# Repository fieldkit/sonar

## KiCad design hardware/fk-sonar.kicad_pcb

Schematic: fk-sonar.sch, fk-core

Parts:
C1, C12: 4.7uF; CAP-0603
C2, C5, C7, C8, C9, C15, C16, C17, C19, C20: 100nF; CAP-0603
C3, C4: 18pF; CAP-0603
C6, C10, C11: 1uF; CAP-0603
C13: 4.7nF; CAP-0603
C14, C18: 10uF; CAP-0603
D1: Orange; LED-0603
D2: PRTR5V0U2X; SOT-143B
D3: Green; LED-0603
F1: MF-PSMF050X-2; MF-PSMF020X
J1: CONN_01x03; Molex_CLIK-Mate_502382-0370_1x03_P1.25mm_Vertical
J2: CONN_02x05_SWD; HDR_02x05_Pitch1.27mm_SMD_SWD
J3: MICRO-USB; USB_10118193-0001LF-core-mod
J4: MICRO-USB; USB_1051330011
J5, J7: CONN_01x02; SJ_OPEN
J6, J12, J13: CONN_01x04; Molex_CLIK-Mate_502382-0470_1x04_P1.25mm_Vertical
J8: CONN_01x03_SERIAL; Molex_CLIK-Mate_502382-0370_1x03_P1.25mm_Vertical
J9, J10: CONN_01x05; Molex_CLIK-Mate_502382-0570_1x05_P1.25mm_Vertical
J11: CONN_01x04; BM04B-SRSS-TB
L1, L2: BLM18KG221SN1D; IND-0603
M1, M3, M4, M6: MOUNT_HOLE; HOLE_NPTH_2.7MM
M2, M5: FIDUCIAL; FIDUCIAL-1MM
Q1: 2N7002LT1G; SOT-23
R1: 2K2; RES-0603
R2, R7, R9: 10K; RES-0603
R3, R5: 330R; RES-0603
R4: 1M; RES-0603
R6, R11, R12: 100K; RES-0603
R8, R10: ?; RES-0603
R13, R14, R15, R16: 4.7K; RES-0603
R17: 2k2; RES-0603
SW1: SPNO; SW_SPST_WURTH_1
U1: ATSAMD21G18A-AU; TQFP-48_7x7mm_Pitch0.5mm
U2: MCP1700T-3302E/MB; SOT-89
U3: TPS2052B; SOIC-8-N
U4: S25FL116K0XMFI041; SOIC-8-N-WIDE
U7: SK6812
Y1: FC-135; ABS07

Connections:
3V3: C5.1, C8.1, C9.1, C11.1, C15.1, D1.2, D3.2, J1.3, J2.1, J5.1, J7.1, J9.1, J10.1, L1.2, R2.1, R6.1, R7.2, R9.2, R13.2, R14.2, U1.17 (VDDIO), U1.36 (VDDIO), U1.44 (VDDIN), U2.3, U3.2, U7.3
5V0: C10.1, C12.1, L2.1, U2.2
/A0: U1.3 (PA02)
/A1: J1.2, U1.7 (PB08)
/A2: U1.8 (PB09)
/A3: U1.9 (PA04), U7.2
/A4: U1.10 (PA05)
/A5: U1.47 (PB02)
/D0: U1.16 (PA11)
/D1: U1.15 (PA10)
/D2_RADIO_CS: U1.23 (PA14)
/D5: U1.24 (PA15)
/D6_FLASH_CS: U1.29 (PA20), U4.1 (~CS~)
/D7_SENSOR_EN: R10.1, U1.30 (PA21), U3.4
/D8_PERIPH_EN: R8.1, U1.11 (PA06), U3.3
/D9: U1.12 (PA07)
/D10: U1.27 (PA18)
/D11: U1.25 (PA16)
/D12: U1.28 (PA19)
/D13: Q1.1, U1.26 (PA17)
/D30: J8.3 (D30), U1.37 (PB22)
/D31: J8.2 (D31), U1.38 (PB23)
/D38_RADIO_D0: U1.22 (PA13)
/MISO: U1.21 (PA12), U4.2 (SO/IO1)
/MOSI: U1.19 (PB10), U4.5 (SI/IO0)
/PERIPH_3V3: C14.1, C16.1, C20.1, J5.2, R11.1, U3.7, U4.3 (~WP~/IO2), U4.7 (~HOLD~/IO3), U4.8 (VCC)
/RESET: R3.1, U1.40 (RESETN)
/RST: C19.1, J2.10, R2.2, R3.2, SW1.2
/RX_LED: U1.48 (PB03)
/SCK: U1.20 (PB11), U4.6 (SCLK)
/SCL1: J6.3, J11.4, J12.3, J13.3, R16.1, U1.32 (PA23)
/SCL3: J9.4, J10.4, R14.1, U1.14 (PA09)
/SDA1: J6.4, J11.3, J12.4, J13.4, R15.1, U1.31 (PA22)
/SDA3: J9.5, J10.5, R13.1, U1.13 (PA08)
/SENSOR_3V3: C17.1, C18.1, J6.1, J7.2, J11.2, J12.1, J13.1, R12.1, R15.2, R16.2, U3.6
/SWCLK: J2.4, U1.45 (PA30)
/SWDIO: J2.2, U1.46 (PA31)
/TX_LED: U1.39 (PA27)
/USB+: D2.2, J3.3, J4.3, U1.34 (PA25)
/USB-: D2.3, J3.2, J4.2, U1.33 (PA24)
/USB_ID: R5.2, U1.41 (PA28)
GND: C1.2, C2.2, C3.1, C4.1, C5.2, C6.2, C7.2, C8.2, C9.2, C10.2, C11.2, C12.2, C13.2, C14.2, C15.2, C16.2, C17.2, C18.2, C19.2, C20.2, D2.1, J1.1, J2.3, J2.5, J2.9, J3.5, J4.5, J6.2, J8.1 (GND), J9.2, J10.2, J11.1, J12.2, J13.2, Q1.2, R4.2, R8.2, R10.2, R11.2, R12.2, R17.2, SW1.1, U1.5 (GNDANA), U1.18 (GND), U1.35 (GND), U1.42 (GND), U2.1, U3.1, U4.4 (VSS), U7.1
unnamed: C1.1, C2.1, U1.4 (PA03)
unnamed: C3.2, U1.2 (PA01), Y1.1
unnamed: C4.2, U1.1 (PA00), Y1.2
unnamed: C6.1, U1.43 (VDDCORE)
unnamed: C7.1, L1.1, U1.6 (VDDANA)
unnamed: C13.1, J3.7, J4.6, R4.1
unnamed: D1.1, R1.1
unnamed: D3.1, R17.1
unnamed: F1.1, L2.2
unnamed: J3.4, J4.4, R5.1, R6.2
unnamed: Q1.3, R1.2
unnamed: R7.1, U3.8
unnamed: R9.1, U3.5
VUSB: D2.4, F1.2, J3.1, J4.1

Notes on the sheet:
MOUNTING
FIDUCIALS
SERIAL FLASH
MCU
TX0
RX0
16Mbit = 2Mbytes
M2.5 size
1.27 mm (0.05")
32.768kHz
12.5pF
LEDS
PERIPHERALS
EXTERNAL SENSORS
CORE CONNECTOR
USB / POWER MANAGEMENT
BUTTONS

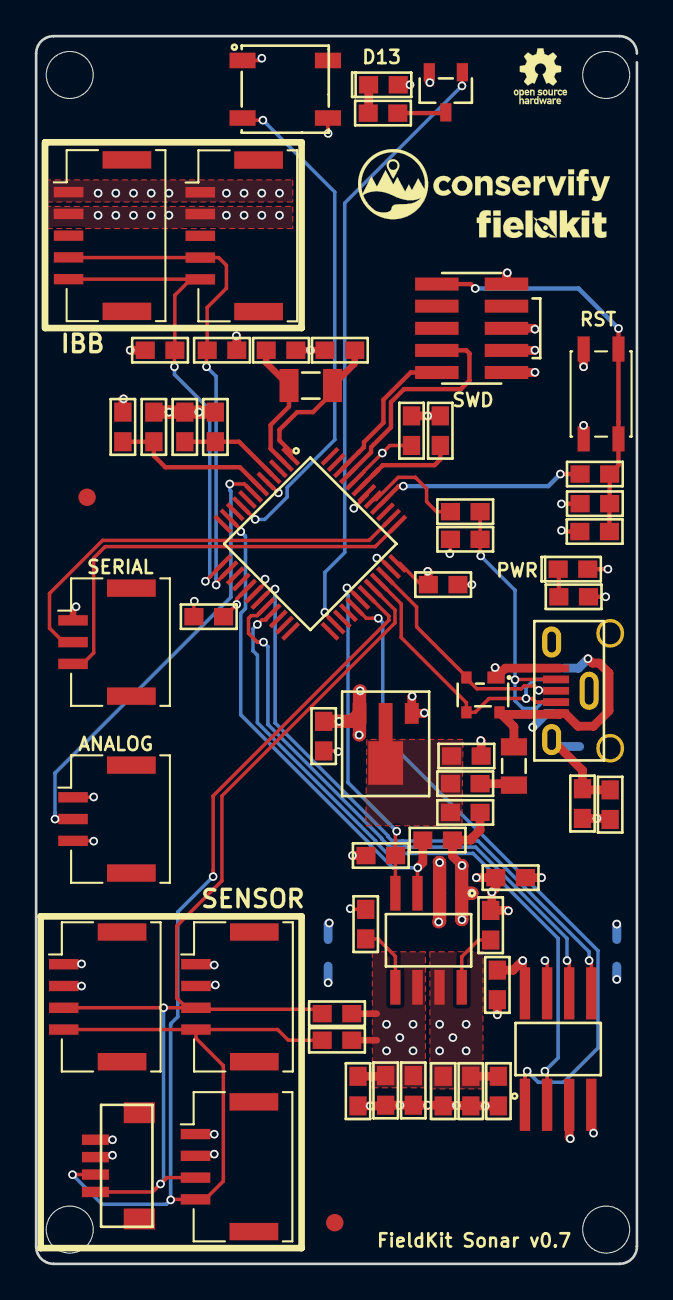
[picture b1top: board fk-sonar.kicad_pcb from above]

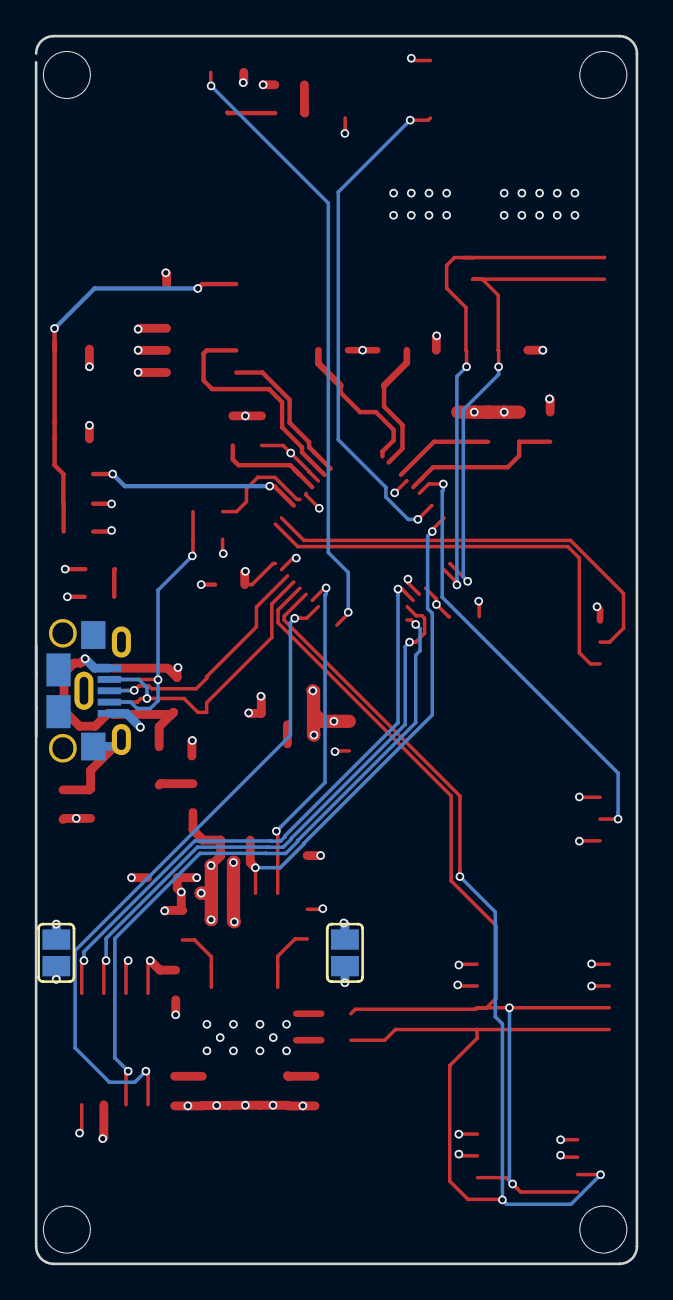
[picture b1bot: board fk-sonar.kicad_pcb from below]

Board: 4 copper layers, 34.5 x 70.5 mm, 70 parts (3 on the bottom side), 41 nets.

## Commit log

2017-11-17 A basic ATSAMD now with an analog sensor connector.
2017-11-17 Copying fk-core, actually and dropping GPS/SD/etc.
2017-11-17 High level layout on the PCB.
2017-11-28 Firmware skeleton.
2017-11-29 The PCB.
2017-12-04 Re-use Makefile patterns.
2017-12-08 Adding gerbers.
2017-12-18 Align the labels on fab layer for easier assembly.
2017-12-18 Quick test firmware.
2017-12-19 New SWD/JTAG programming footprint to avoid confusion.
2017-12-19 Using our MICRO-USB with the larger, non oval drills.
2017-12-19 Adding a solar panel connector. Just a JST below the battery JST.
2017-12-20 Fix led pin. This one uses A2, A4, A5, and D13.
2017-12-20 Labels on SDA/SCL header. Also made GND the square pad.
    No room for the label there.
2017-12-22 Easier fab label placements.
2017-12-28 Just some cleanup. Fix the fuel gauge lines.
2017-12-29 Exposing D30/D31 (as test points because stuff is kind of cramped)
    If this becomes more regular/useful I'll make them pins or use a header.
2018-05-01 Switch to our RadioHead fork.
2018-05-01 Disable verbose makefiles.
2018-05-04 Fix USB footprint. Add a Molex for D30/D31 serial.
2018-05-21 Updating BOM details.
2018-06-29 Change orientation of sonar sensor connector. Matches the harness we have.
2018-07-03 Adding main connector and mounting holes. Bump version to v0.3
2018-07-03 Basic firmware, reading math copied from Okavango test code.
2018-07-10 Plotting gerbers.
2018-07-24 Upgrade to Kicad 5. Also adding SK6812 and molex connectors.
2018-07-24 Remove old logo in wks.
2018-07-24 Silkscreen cleanup.
2018-07-24 Schematic layout.
2018-07-24 Add lwcron dependency.
2018-07-25 Pass firmware/build info in.
2018-07-27 New USB for vertical entry.
2018-07-30 Use latest dependencies.
2018-07-30 Rename target.
2018-07-30 Add number of readings and module name to info.
2018-07-31 Use new allocation strategy for ModuleInfo.
2018-08-02 Ignore dependencies.cmake
2018-08-03 Add Jenkinsfile.
2018-08-08 Trigger distribution job.
2018-08-08 Dependency fixes.
2018-08-08 Add build triggers.
2018-08-09 Not waiting on distribution build.
2018-08-09 Use helper for updating distribution site.
2018-08-11 Compile flags to enable flash in phylum.
2018-08-13 Compile flags for phylum.
2018-08-14 Add distribute step.
2018-08-15 Archive binaries.
2018-08-20 Set firmware compiled time.
2018-08-21 Use new Arduino CMake stuff.
2018-08-21 Pass path spec to archive.
2018-08-21 Set firmware directory for distribution.
2018-08-22 Consistent part values across our schematics.
2018-08-22 Part updates.
2018-08-23 Use repository URLs for all deps.
2018-08-24 Use repository URLs for deps.
2018-08-24 Use tools name for dependencies.sd.
2018-08-24 Fix SK6812. Assign easier to read labels to signals.
2018-08-24 Align connectors on side. Add periph switch.
2018-08-24 Fixing rescued stuff and DRC checks.
2018-08-25 Same dependencies in test firmware.
2018-08-28 Updated to use state instead of callbacks.
2018-08-28 Split module into its own file.
2018-08-28 Use more compatible FP for flash.
2018-08-28 Consistency in part values
2018-08-28 Add NeoPixel dependency.
2018-09-07 Bump version and plot gerbers.
2018-09-26 Pin to newer library versions.
2018-09-27 Specify flash state struct.
2018-10-04 Fix test's flash pin number. Log raw values from sensor during test.
2018-10-04 Use standard module bus selected, picking 11/13 and 4/3.
2018-10-04 Include raw value in data.
2018-10-04 Disable flash for now.
2018-10-04 Toggle peripherals. Also fix startup hang in module.
2018-10-24 Pass peripherals enable pin to Module to control flash.
2018-10-24 Don't need namespace qualifier anymore.
2018-10-24 Rename default module firmware to include standard profile name.
2018-10-24 Fix size of sensor readings array. Was off.
    This was causing us to blow away memory, and so we'd fail when taking the
    second reading. FK-507
    This should really be hard to fall victim to.
2018-10-25 Log to Debug if opening USB Serial fails.
2018-11-01 Set required uptime parameter.
2018-11-07 Adding some pull downs.
2018-11-19 Moving labels around.
2018-11-27 Take 3 readings by default.
2018-12-04 Add orientation indicator to SWD fp.
2018-12-04 Switch to 2.7mm mounting holes.
2018-12-11 Removing I2C3 support that none of our boards use.
2018-12-12 Adding a board definition.
2018-12-12 Fix make jobserver warnings.
2018-12-20 Started removing unused portion of the design (battery and Lora)
2018-12-26 Deleted charging, LoRa, fuel gauge, swapped out connectors and peripheral switch
2018-12-26 Finished rough placement of components, starting trace routing
2018-12-26 Finished routing traces, starting DRC
2018-12-26 Finished DRC
2018-12-26 Cleaned up schematic with labeling and dividers
2018-12-26 Generated gerbes for v0.7
2019-01-02 Changed board outline slightly to be on a 0.5 mm grid (for panelization)
2019-01-02 Regenerated gerber files before moving to panelization
2019-01-02 Shifted board to fit onto the grid better (mounting holes have not moved in either move)
2019-01-02 Created 03x03 panelized version of fk-sonar v0.07 with gerbers
2019-01-23 Drop fuel gauge and radio test. No longer on the board.
2019-02-12 Lots of test cleanup, move reading interpretion code to common.
2019-02-12 Cleaning up the sonar reading math.
2019-02-19 Archive test firmware.
2019-02-25 Upgrade nanopb.
2019-03-13 Fixed missing resistor values.
2019-03-15 Script to flash and test.
2019-04-18 Fix bad array size, causing crashes.
2019-04-23 Use absolute BUILD in Makefile.
